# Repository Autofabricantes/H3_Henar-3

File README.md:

Hi! Welcome to the **_Henar#3 Wiki_**, please read carefully this welcome page that describes the full content of the _Wiki_.

This repository is still under construction (after many months, I know :'( ) Please if whatever doubt you have is not yet solved contact us somehow (email, Github, etc)

# Project Scope
The **_Henar#3_** is a _Open Source_ MIDI percussion instrument designed to perform live. Its main characteristics are:
* **Open Source:** The **_Henar#3_** has been designed and build with **_Open Source_** HW and SW and using accesible manufacturing technologies in order for it to be very affordable and easily moded.
* **Build Flexibility:** The **_Henar#3_** has been designed to allow a large number of different configurations (HMI elements in order to cope with the specific necessities of each user.
* **Stand Alone:** The **_Henar#3_** is an instrument designed to be played live, therefore it is a _Plug&Play_ device which does not need of extra elements to be played.
* **Periperic Flexibility:** Besides being a _Plug&Play_ device, the **_Henar#3_** allows its connection with other sound devices such as speakers and alternative MIDI devices.

# History and Collaborators
The **_Henar#3_** is part of a longer project started by the **_Celeo Proyectos_** and **_Un Instrumento para Henar_** in 2015. Its initial objective is to build a proper adapted instrument for Henar, a woman from Cuenca (Spain) that plays in an orchestra.

Apart from the instrument (which has two previous versions which will be described later) the project aims to build up a platform for the community of developers, users and enthusiasts to work together towards new ways to socialize with music and make it accesible for everyone. This is achieved not only through the development of the instrument itself but also through the creation of didactic materials and the organization of events such as **_DiverS+S 2017_** (http://www.diversos.eu/), where various projects were presented and put in common, in order to create links and an active net.

The collaborators of this project are:
## Celeo Proyectos

## Un instrumento para Henar

### Website: www.centroceleo.es/henar
### Contact: uninstrumentoparahenar@gmail.com

## Autofabricantes
**_Autofabricantes_** in an association based in _Medialab-Prado_, Madrid. It develops several _Open Source_ technological solutions in the medical and accesibility field. It's main development lines right now are:
* Myoelectric Hand Prothesis for children.
* 3D printed hand prosthesis for children (both experimental like __SuperGizz__ and standard).
* **_Henar#3_** instrument (The one this Wiki covers).

### Website: www.autofabricantes.org
### Contact: info@autofabricantes.org

## Escuela de Oficios Electrosonoros
_**Escuela de Oficios Electrosonoros**_ (in eng. _**School for Electrosonic Crafts**_) is an artistic and educational project that works to make electronic music (or music made with technology in general) accesible to everyone. 

*  Elaborate a feministic (or better just... diverse) history of electronic music.
*  Develop pedagogical tools for teaching electronic music in schools.
*  Research about accessibility of electronic music.

### Website: www.oficioselectrosonoros.org
### Contact: gurrupibaby@gmail.com

# About the previous Henar (Henar#1, Henar#2)
The Un instrumento para Henar project has already developed two previous versions of the instruments.

## Henar#1: [HERE LINK]
## Henar#2: [HERE LINK]

The **_Henar#3_** improvement objetives are:
* Increase System flexibility.
* Easier Assembly and manufacturing.
* Easier MIDI configuration.
* Improved ergonomy.

# Scope of the Wiki
This _Wiki_ aims to concentrate all the knowledge of the project. This covers:
* Global description of the project and its subsystems.
* Description of all the files in the repository.
* Description of all the elements and their evolution.
* **Assembly Guide** of all the elements (HW, SW, Mechanical).
* Tutorials and other didactic material.

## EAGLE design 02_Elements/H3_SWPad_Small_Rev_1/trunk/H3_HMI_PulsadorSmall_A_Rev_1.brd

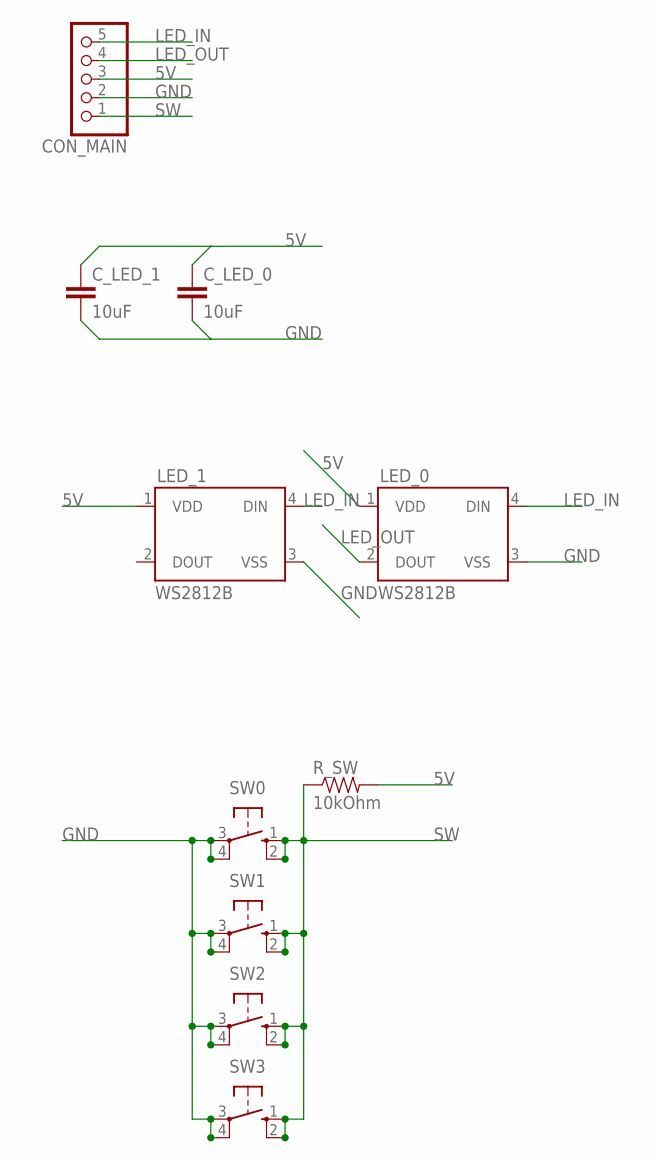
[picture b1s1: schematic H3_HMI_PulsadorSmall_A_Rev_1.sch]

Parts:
CON_MAIN: PINHD-1X5/90; 1X05/90
C_LED_0, C_LED_1: 10uF; C1206
LED_0, LED_1: WS2812B
R_SW: 10kOhm; 1206
SW0, SW1, SW2, SW3: 10-XX; B3F-10XX

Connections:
5V: CON_MAIN.3, C_LED_0.1, C_LED_1.1, LED_0.1 (VDD), LED_1.1 (VDD), R_SW.2
GND: CON_MAIN.2, C_LED_0.2, C_LED_1.2, LED_0.3 (VSS), LED_1.3 (VSS), SW0.3, SW0.4 (P1), SW1.3, SW1.4 (P1), SW2.3, SW2.4 (P1), SW3.3, SW3.4 (P1)
LED_IN: CON_MAIN.5, LED_0.4 (DIN), LED_1.4 (DIN)
LED_OUT: CON_MAIN.4, LED_0.2 (DOUT)
SW: CON_MAIN.1, R_SW.1, SW0.1 (S), SW0.2 (S1), SW1.1 (S), SW1.2 (S1), SW2.1 (S), SW2.2 (S1), SW3.1 (S), SW3.2 (S1)

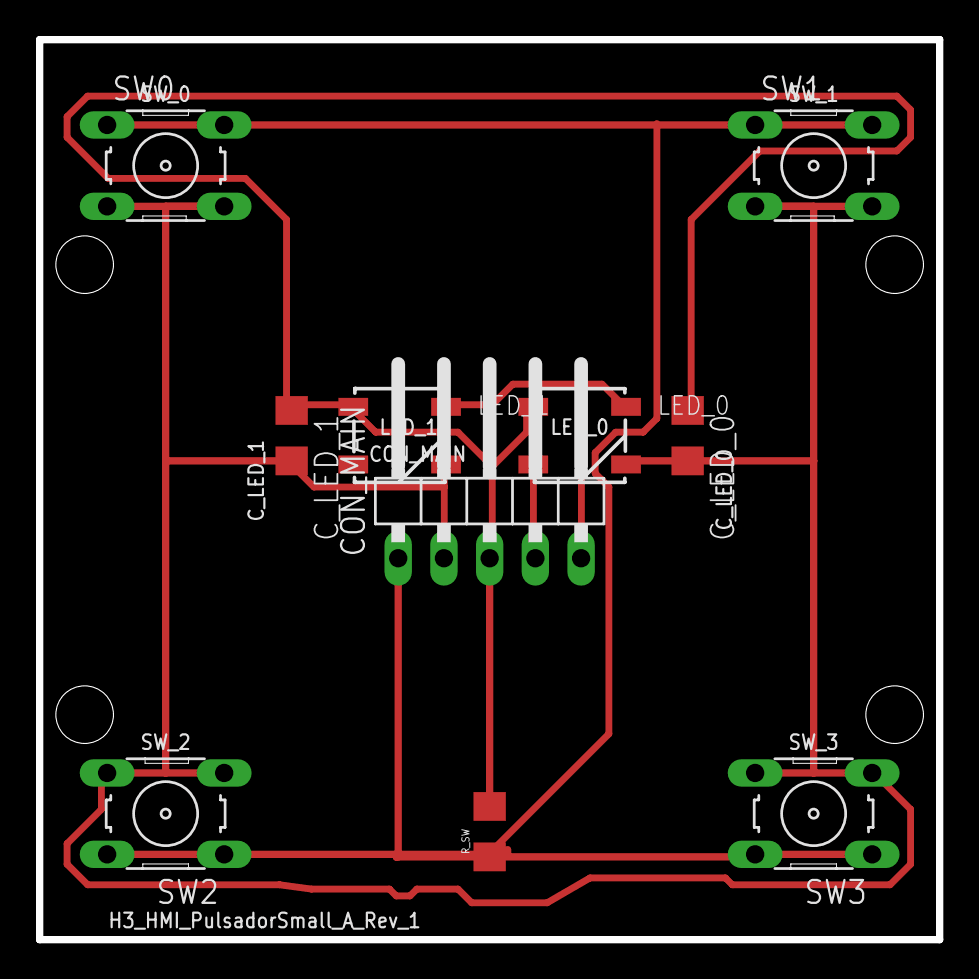
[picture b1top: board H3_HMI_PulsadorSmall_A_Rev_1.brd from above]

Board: 2 copper layers, 50.0 x 50.0 mm, 10 parts (0 on the bottom side), 5 nets.

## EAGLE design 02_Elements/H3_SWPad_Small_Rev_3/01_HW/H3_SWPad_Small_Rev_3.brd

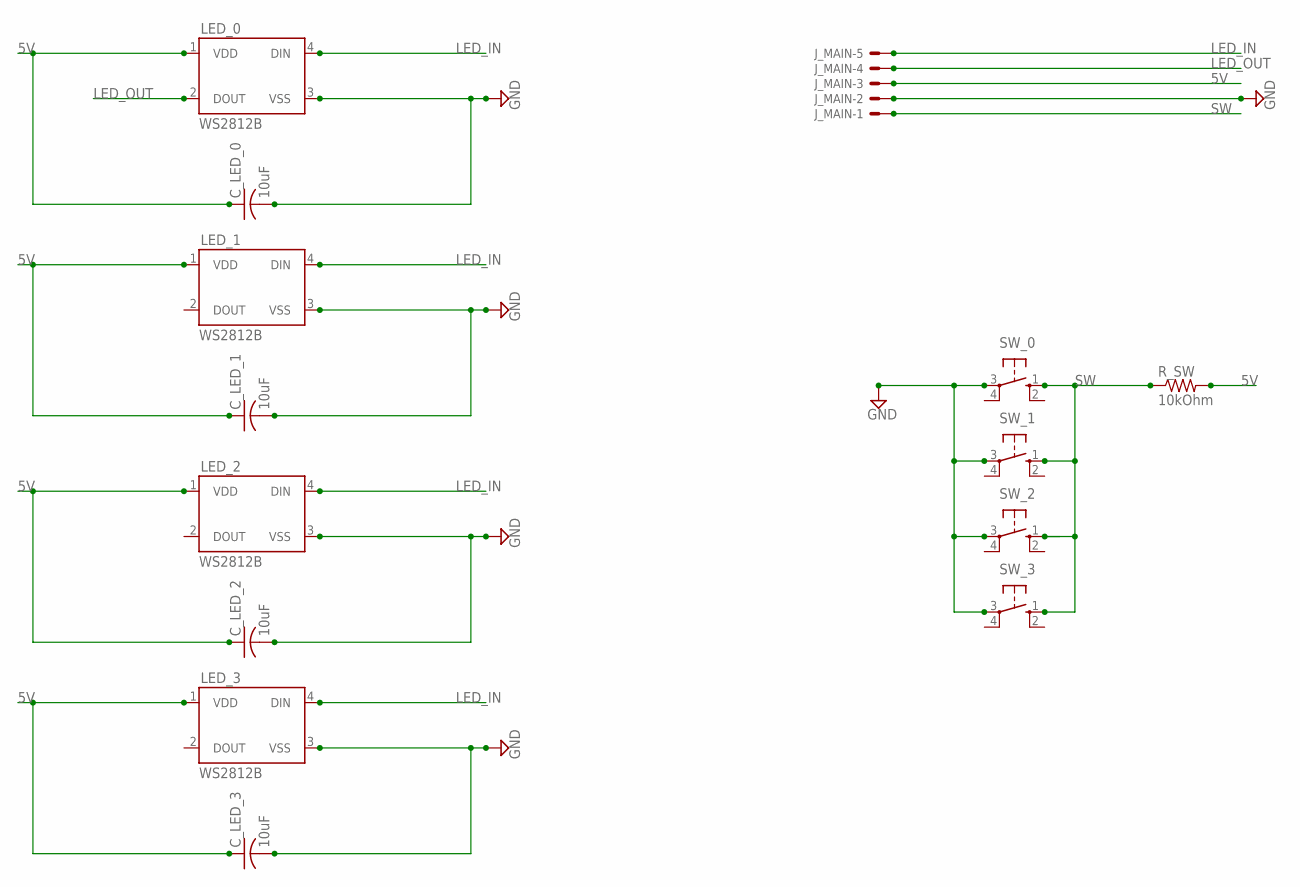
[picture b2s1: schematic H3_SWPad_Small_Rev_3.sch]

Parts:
C_LED_0, C_LED_1, C_LED_2, C_LED_3: 10uF; C1206K
J_MAIN: 22-05-7058-05; 7395-05
LED_0, LED_1, LED_2, LED_3: WS2812B
R_SW: 10kOhm; R1206W
SW_0, SW_1, SW_2, SW_3: 10-XX; B3F-10XX

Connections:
5V: C_LED_0.1, C_LED_1.1, C_LED_2.1, C_LED_3.1, J_MAIN.3, LED_0.1 (VDD), LED_1.1 (VDD), LED_2.1 (VDD), LED_3.1 (VDD), R_SW.2
GND: C_LED_0.2, C_LED_1.2, C_LED_2.2, C_LED_3.2, J_MAIN.2, LED_0.3 (VSS), LED_1.3 (VSS), LED_2.3 (VSS), LED_3.3 (VSS), SW_0.3, SW_1.3, SW_2.3, SW_3.3
LED_IN: J_MAIN.5, LED_0.4 (DIN), LED_1.4 (DIN), LED_2.4 (DIN), LED_3.4 (DIN)
LED_OUT: J_MAIN.4, LED_0.2 (DOUT)
SW: J_MAIN.1, R_SW.1, SW_0.1 (S), SW_1.1 (S), SW_2.1 (S), SW_3.1 (S)

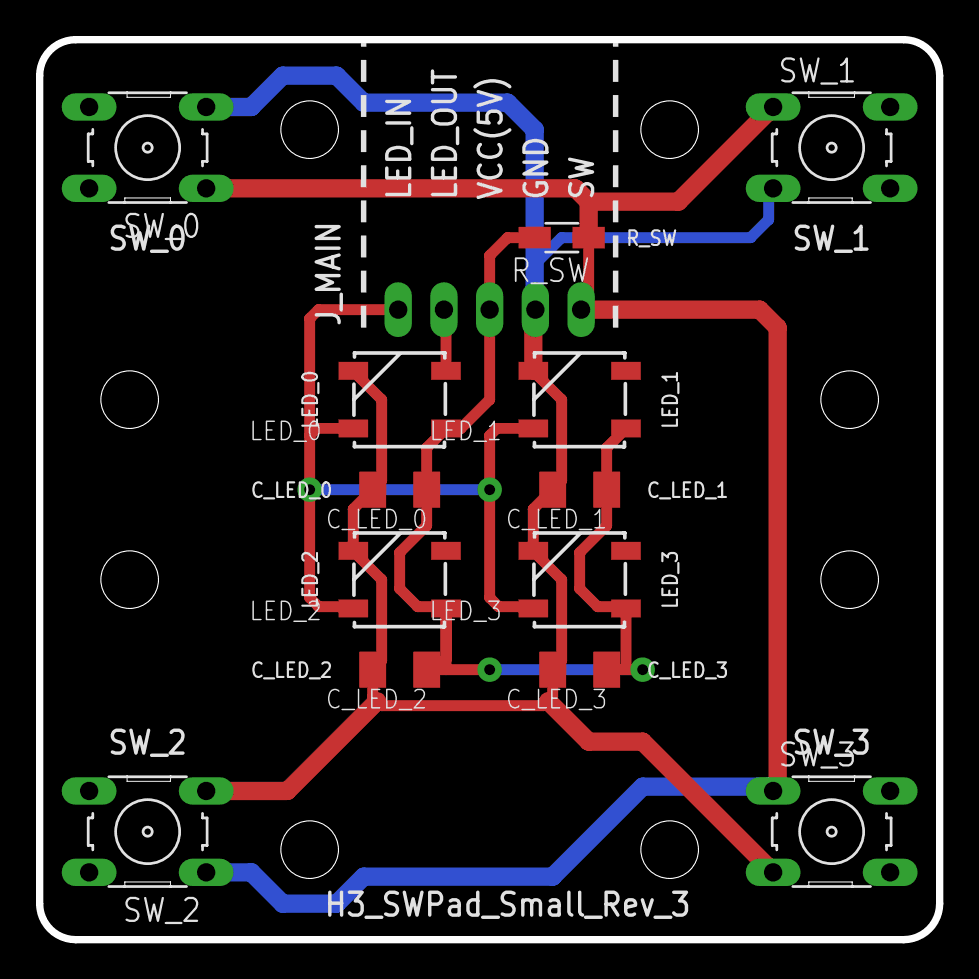
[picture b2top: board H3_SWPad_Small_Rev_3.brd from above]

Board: 2 copper layers, 50.0 x 50.0 mm, 14 parts (1 on the bottom side), 5 nets.

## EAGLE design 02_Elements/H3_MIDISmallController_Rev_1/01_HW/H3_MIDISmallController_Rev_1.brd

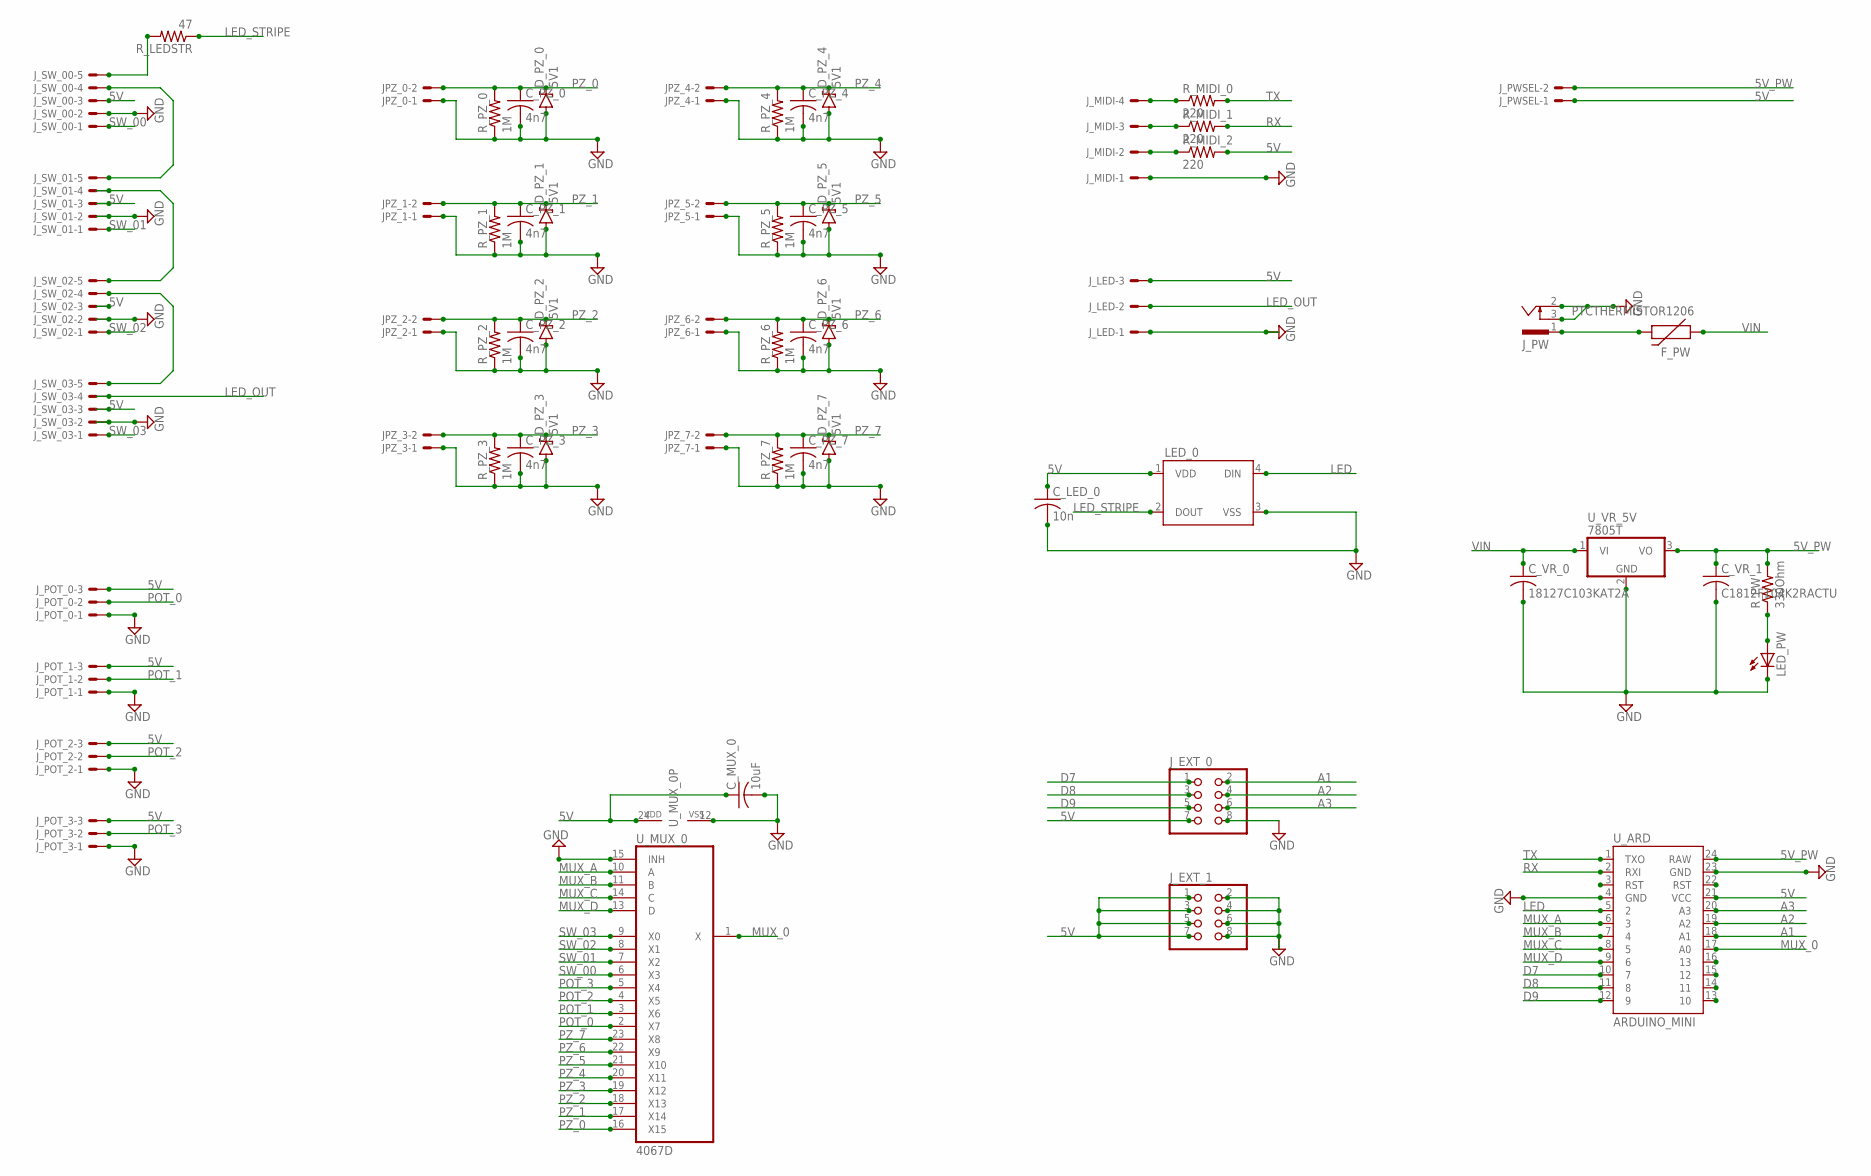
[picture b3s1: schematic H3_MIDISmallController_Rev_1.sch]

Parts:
C_LED_0: 10n; C1206
C_MUX_0: 10uF; C1206K
C_PZ_0, C_PZ_1, C_PZ_2, C_PZ_3, C_PZ_4, C_PZ_5, C_PZ_6, C_PZ_7: 4n7; C1206
C_VR_0: 18127C103KAT2A; C1206
C_VR_1: C1812F104K2RACTU; C1206
D_PZ_0, D_PZ_1, D_PZ_2, D_PZ_3, D_PZ_4, D_PZ_5, D_PZ_6, D_PZ_7: 5V1; DIODE-BZT52
F_PW: PTCTHERMISTOR1206; PTC-1206
JPZ_0, JPZ_1, JPZ_2, JPZ_3, JPZ_4, JPZ_5, JPZ_6, JPZ_7: 22-05-7028-02; 7395-02
J_EXT_0, J_EXT_1: PINHD-2X4/90; 2X04/90
J_LED: 22-05-7038-03; 7395-03
J_MIDI: 22-05-7048-04; 7395-04
J_POT_0, J_POT_1, J_POT_2, J_POT_3: 22-05-7038-03; 7395-03
J_PW: SCD-014A; SCD-014-A
J_PWSEL: 22-05-7028-02; 7395-02
J_SW_00, J_SW_01, J_SW_02, J_SW_03: 22-05-7058-05; 7395-05
LED_0: WS2812B
LED_PW: LEDSMT1206; 1206
R_LEDSTR: 47; M1206
R_MIDI_0, R_MIDI_1, R_MIDI_2: 220; M1206
R_PW: 330Ohm; M1206
R_PZ_0, R_PZ_1, R_PZ_2, R_PZ_3, R_PZ_4, R_PZ_5, R_PZ_6, R_PZ_7: 1M; M1206
U_ARD: ARDUINO_MINI
U_MUX_0: 4067D; SO24W
U_VR_5V: 7805T; TO220H

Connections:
5V: C_LED_0.1, C_MUX_0.1, J_EXT_0.7, J_EXT_1.1, J_EXT_1.3, J_EXT_1.5, J_EXT_1.7, J_LED.3, J_POT_0.3, J_POT_1.3, J_POT_2.3, J_POT_3.3, J_PWSEL.1, J_SW_00.3, J_SW_01.3, J_SW_02.3, J_SW_03.3, LED_0.1 (VDD), R_MIDI_2.2, U_ARD.21 (VCC), U_MUX_0.24 (VDD)
5V_PW: C_VR_1.1, J_PWSEL.2, R_PW.2, U_ARD.24 (RAW), U_VR_5V.3 (VO)
A1: J_EXT_0.2, U_ARD.18 (A1)
A2: J_EXT_0.4, U_ARD.19 (A2)
A3: J_EXT_0.6, U_ARD.20 (A3)
D7: J_EXT_0.1, U_ARD.10 (7)
D8: J_EXT_0.3, U_ARD.11 (8)
D9: J_EXT_0.5, U_ARD.12 (9)
GND: C_LED_0.2, C_MUX_0.2, C_PZ_0.2, C_PZ_1.2, C_PZ_2.2, C_PZ_3.2, C_PZ_4.2, C_PZ_5.2, C_PZ_6.2, C_PZ_7.2, C_VR_0.2, C_VR_1.2, D_PZ_0.A, D_PZ_1.A, D_PZ_2.A, D_PZ_3.A, D_PZ_4.A, D_PZ_5.A, D_PZ_6.A, D_PZ_7.A, JPZ_0.1, JPZ_1.1, JPZ_2.1, JPZ_3.1, JPZ_4.1, JPZ_5.1, JPZ_6.1, JPZ_7.1, J_EXT_0.8, J_EXT_1.2, J_EXT_1.4, J_EXT_1.6, J_EXT_1.8, J_LED.1, J_MIDI.1, J_POT_0.1, J_POT_1.1, J_POT_2.1, J_POT_3.1, J_PW.2, J_PW.3, J_SW_00.2, J_SW_01.2, J_SW_02.2, J_SW_03.2, LED_0.3 (VSS), LED_PW.C, R_PZ_0.1, R_PZ_1.1, R_PZ_2.1, R_PZ_3.1, R_PZ_4.1, R_PZ_5.1, R_PZ_6.1, R_PZ_7.1, U_ARD.4 (GND), U_ARD.23 (GND), U_MUX_0.12 (VSS), U_MUX_0.15 (INH), U_VR_5V.2 (GND)
LED: LED_0.4 (DIN), U_ARD.5 (2)
LED_IN2: J_SW_01.4, J_SW_02.5
LED_OUT: J_LED.2, J_SW_03.4
LED_STRIPE: LED_0.2 (DOUT), R_LEDSTR.1
MUX_0: U_ARD.17 (A0), U_MUX_0.1 (X)
MUX_A: U_ARD.6 (3), U_MUX_0.10 (A)
MUX_B: U_ARD.7 (4), U_MUX_0.11 (B)
MUX_C: U_ARD.8 (5), U_MUX_0.14 (C)
MUX_D: U_ARD.9 (6), U_MUX_0.13 (D)
unnamed: LED_PW.A, R_PW.1
unnamed: J_SW_00.4, J_SW_01.5
unnamed: J_SW_00.5, R_LEDSTR.2
unnamed: J_SW_02.4, J_SW_03.5
unnamed: F_PW.2, J_PW.1
unnamed: J_MIDI.2, R_MIDI_2.1
unnamed: J_MIDI.3, R_MIDI_1.1
unnamed: J_MIDI.4, R_MIDI_0.1
POT_0: J_POT_0.2, U_MUX_0.2 (X7)
POT_1: J_POT_1.2, U_MUX_0.3 (X6)
POT_2: J_POT_2.2, U_MUX_0.4 (X5)
POT_3: J_POT_3.2, U_MUX_0.5 (X4)
PZ_0: C_PZ_0.1, D_PZ_0.C, JPZ_0.2, R_PZ_0.2, U_MUX_0.16 (X15)
PZ_1: C_PZ_1.1, D_PZ_1.C, JPZ_1.2, R_PZ_1.2, U_MUX_0.17 (X14)
PZ_2: C_PZ_2.1, D_PZ_2.C, JPZ_2.2, R_PZ_2.2, U_MUX_0.18 (X13)
PZ_3: C_PZ_3.1, D_PZ_3.C, JPZ_3.2, R_PZ_3.2, U_MUX_0.19 (X12)
PZ_4: C_PZ_4.1, D_PZ_4.C, JPZ_4.2, R_PZ_4.2, U_MUX_0.20 (X11)
PZ_5: C_PZ_5.1, D_PZ_5.C, JPZ_5.2, R_PZ_5.2, U_MUX_0.21 (X10)
PZ_6: C_PZ_6.1, D_PZ_6.C, JPZ_6.2, R_PZ_6.2, U_MUX_0.22 (X9)
PZ_7: C_PZ_7.1, D_PZ_7.C, JPZ_7.2, R_PZ_7.2, U_MUX_0.23 (X8)
RX: R_MIDI_1.2, U_ARD.2 (RXI)
SW_00: J_SW_00.1, U_MUX_0.6 (X3)
SW_01: J_SW_01.1, U_MUX_0.7 (X2)
SW_02: J_SW_02.1, U_MUX_0.8 (X1)
SW_03: J_SW_03.1, U_MUX_0.9 (X0)
TX: R_MIDI_0.2, U_ARD.1 (TXO)
VIN: C_VR_0.1, F_PW.1, U_VR_5V.1 (VI)

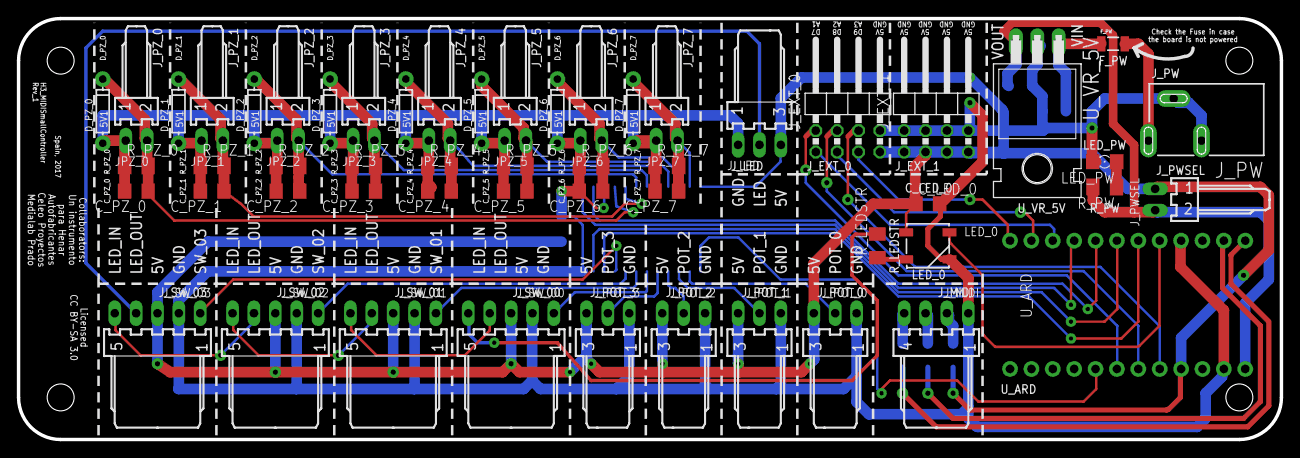
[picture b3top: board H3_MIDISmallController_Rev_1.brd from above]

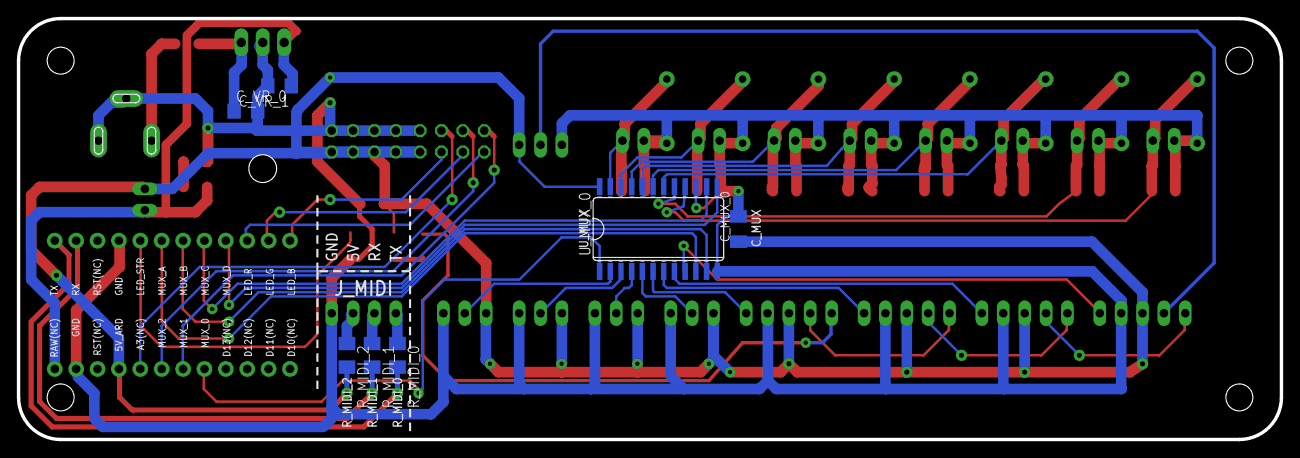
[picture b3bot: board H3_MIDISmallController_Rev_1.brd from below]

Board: 2 copper layers, 150.0 x 50.0 mm, 61 parts (7 on the bottom side), 45 nets.

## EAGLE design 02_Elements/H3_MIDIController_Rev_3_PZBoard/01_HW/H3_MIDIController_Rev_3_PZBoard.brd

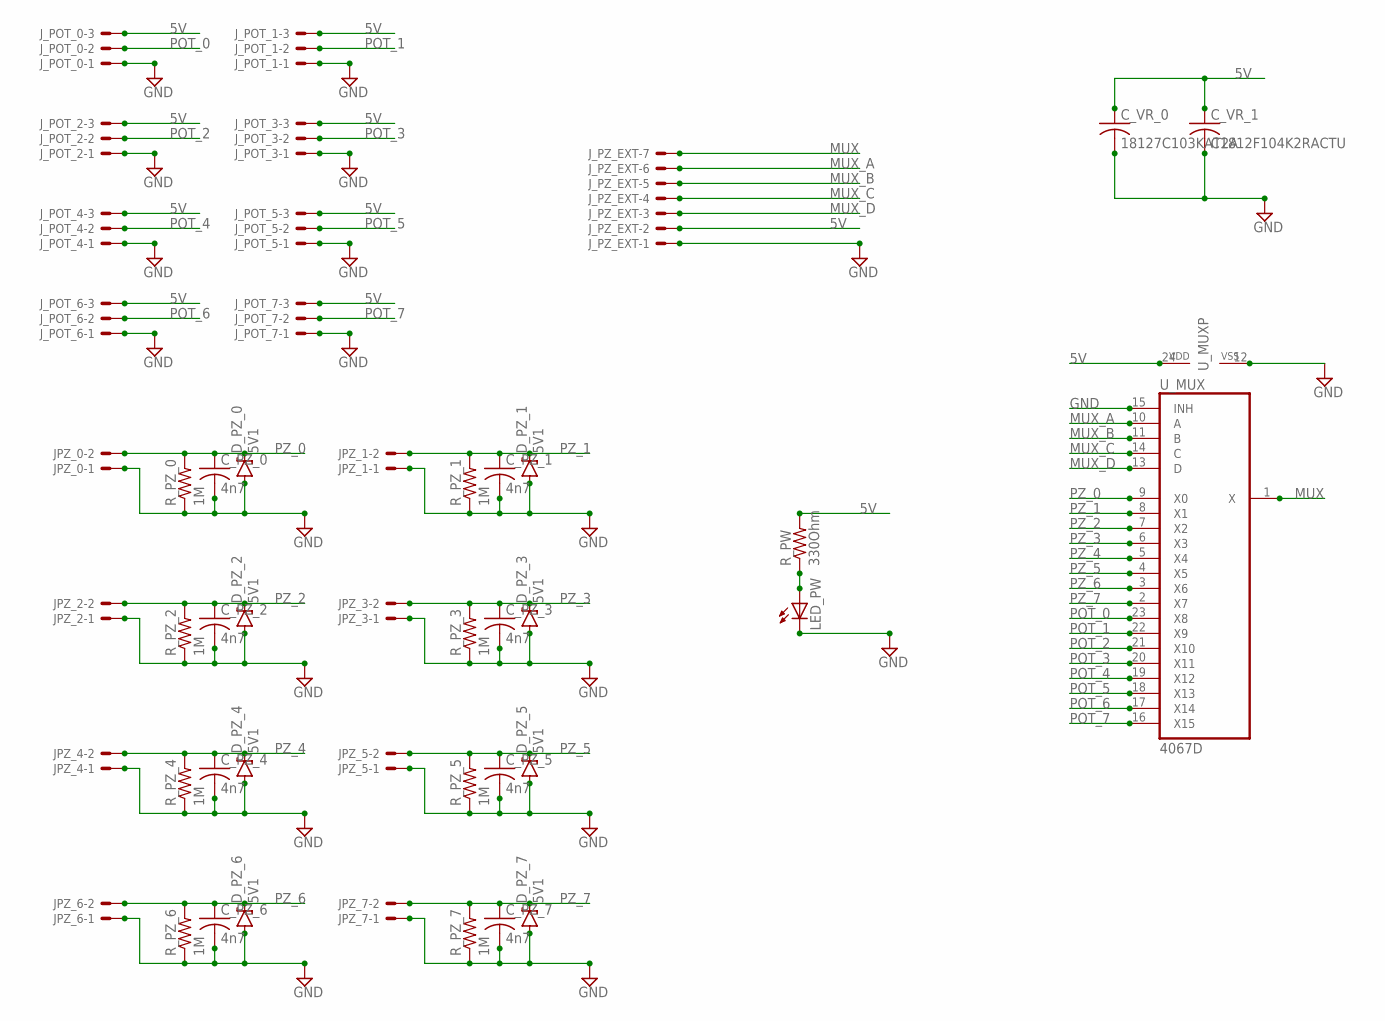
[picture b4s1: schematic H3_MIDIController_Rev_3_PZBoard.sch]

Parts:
C_PZ_0, C_PZ_1, C_PZ_2, C_PZ_3, C_PZ_4, C_PZ_5, C_PZ_6, C_PZ_7: 4n7; C1206
C_VR_0: 18127C103KAT2A; C1812K
C_VR_1: C1812F104K2RACTU; C1812K
D_PZ_0, D_PZ_1, D_PZ_2, D_PZ_3, D_PZ_4, D_PZ_5, D_PZ_6, D_PZ_7: 5V1; DIODE-BZT52
JPZ_0, JPZ_1, JPZ_2, JPZ_3, JPZ_4, JPZ_5, JPZ_6, JPZ_7: 22-05-7028-02; 7395-02
J_POT_0, J_POT_1, J_POT_2, J_POT_3, J_POT_4, J_POT_5, J_POT_6, J_POT_7: 22-05-7038-03; 7395-03
J_PZ_EXT: 22-05-7078-07; 7395-07
LED_PW: LEDSMT1206; 1206
R_PW: 330Ohm; M1206
R_PZ_0, R_PZ_1, R_PZ_2, R_PZ_3, R_PZ_4, R_PZ_5, R_PZ_6, R_PZ_7: 1M; M1206
U_MUX: 4067D; SO24W

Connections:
5V: C_VR_0.1, C_VR_1.1, J_POT_0.3, J_POT_1.3, J_POT_2.3, J_POT_3.3, J_POT_4.3, J_POT_5.3, J_POT_6.3, J_POT_7.3, J_PZ_EXT.2, R_PW.2, U_MUX.24 (VDD)
GND: C_PZ_0.2, C_PZ_1.2, C_PZ_2.2, C_PZ_3.2, C_PZ_4.2, C_PZ_5.2, C_PZ_6.2, C_PZ_7.2, C_VR_0.2, C_VR_1.2, D_PZ_0.A, D_PZ_1.A, D_PZ_2.A, D_PZ_3.A, D_PZ_4.A, D_PZ_5.A, D_PZ_6.A, D_PZ_7.A, JPZ_0.1, JPZ_1.1, JPZ_2.1, JPZ_3.1, JPZ_4.1, JPZ_5.1, JPZ_6.1, JPZ_7.1, J_POT_0.1, J_POT_1.1, J_POT_2.1, J_POT_3.1, J_POT_4.1, J_POT_5.1, J_POT_6.1, J_POT_7.1, J_PZ_EXT.1, LED_PW.C, R_PZ_0.1, R_PZ_1.1, R_PZ_2.1, R_PZ_3.1, R_PZ_4.1, R_PZ_5.1, R_PZ_6.1, R_PZ_7.1, U_MUX.12 (VSS), U_MUX.15 (INH)
MUX: J_PZ_EXT.7, U_MUX.1 (X)
MUX_A: J_PZ_EXT.6, U_MUX.10 (A)
MUX_B: J_PZ_EXT.5, U_MUX.11 (B)
MUX_C: J_PZ_EXT.4, U_MUX.14 (C)
MUX_D: J_PZ_EXT.3, U_MUX.13 (D)
unnamed: LED_PW.A, R_PW.1
POT_0: J_POT_0.2, U_MUX.23 (X8)
POT_1: J_POT_1.2, U_MUX.22 (X9)
POT_2: J_POT_2.2, U_MUX.21 (X10)
POT_3: J_POT_3.2, U_MUX.20 (X11)
POT_4: J_POT_4.2, U_MUX.19 (X12)
POT_5: J_POT_5.2, U_MUX.18 (X13)
POT_6: J_POT_6.2, U_MUX.17 (X14)
POT_7: J_POT_7.2, U_MUX.16 (X15)
PZ_0: C_PZ_0.1, D_PZ_0.C, JPZ_0.2, R_PZ_0.2, U_MUX.9 (X0)
PZ_1: C_PZ_1.1, D_PZ_1.C, JPZ_1.2, R_PZ_1.2, U_MUX.8 (X1)
PZ_2: C_PZ_2.1, D_PZ_2.C, JPZ_2.2, R_PZ_2.2, U_MUX.7 (X2)
PZ_3: C_PZ_3.1, D_PZ_3.C, JPZ_3.2, R_PZ_3.2, U_MUX.6 (X3)
PZ_4: C_PZ_4.1, D_PZ_4.C, JPZ_4.2, R_PZ_4.2, U_MUX.5 (X4)
PZ_5: C_PZ_5.1, D_PZ_5.C, JPZ_5.2, R_PZ_5.2, U_MUX.4 (X5)
PZ_6: C_PZ_6.1, D_PZ_6.C, JPZ_6.2, R_PZ_6.2, U_MUX.3 (X6)
PZ_7: C_PZ_7.1, D_PZ_7.C, JPZ_7.2, R_PZ_7.2, U_MUX.2 (X7)

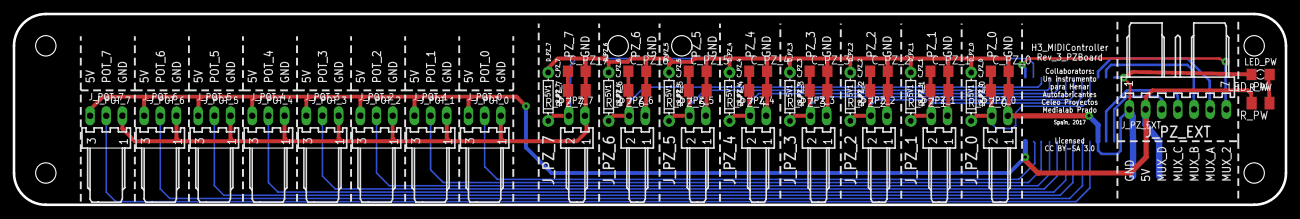
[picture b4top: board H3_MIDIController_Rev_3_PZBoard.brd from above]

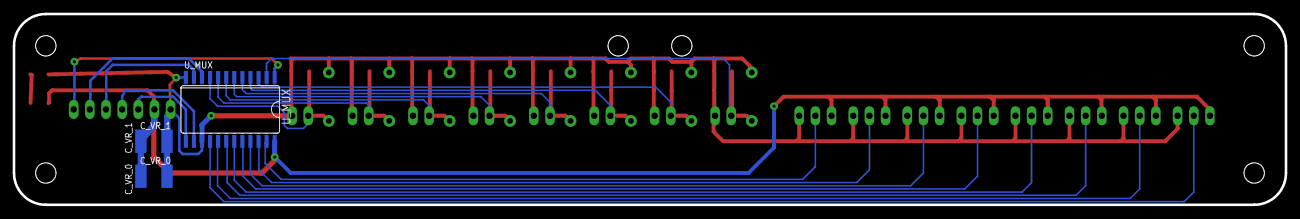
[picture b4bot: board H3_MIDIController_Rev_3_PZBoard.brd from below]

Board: 2 copper layers, 200.0 x 30.0 mm, 46 parts (3 on the bottom side), 24 nets.

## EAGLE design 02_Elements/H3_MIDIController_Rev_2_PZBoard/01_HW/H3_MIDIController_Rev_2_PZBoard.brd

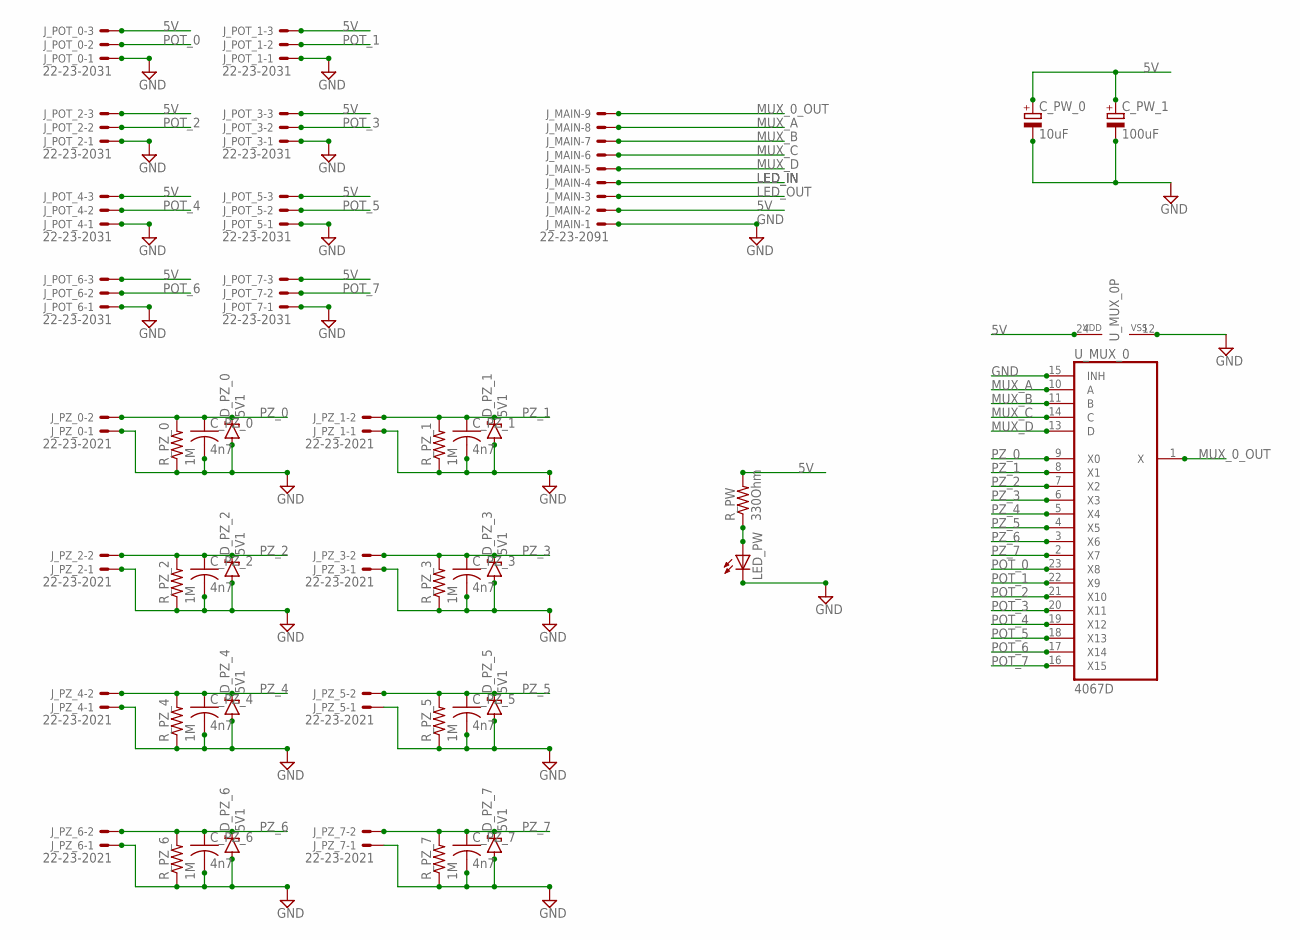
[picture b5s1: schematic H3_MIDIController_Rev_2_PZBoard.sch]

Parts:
C_PW_0: 10uF; TT2D6L
C_PW_1: 100uF; TT2D6L
C_PZ_0, C_PZ_1, C_PZ_2, C_PZ_3, C_PZ_4, C_PZ_5, C_PZ_6, C_PZ_7: 4n7; C1206
D_PZ_0, D_PZ_1, D_PZ_2, D_PZ_3, D_PZ_4, D_PZ_5, D_PZ_6, D_PZ_7: 5V1; DIODE-BZT52
J_MAIN: 22-23-2091
J_POT_0, J_POT_1, J_POT_2, J_POT_3, J_POT_4, J_POT_5, J_POT_6, J_POT_7: 22-23-2031
J_PZ_0, J_PZ_1, J_PZ_2, J_PZ_3, J_PZ_4, J_PZ_5, J_PZ_6, J_PZ_7: 22-23-2021
LED_PW: LEDSMT1206; 1206
R_PW: 330Ohm; M1206
R_PZ_0, R_PZ_1, R_PZ_2, R_PZ_3, R_PZ_4, R_PZ_5, R_PZ_6, R_PZ_7: 1M; M1206
U_MUX_0: 4067D; SO24W

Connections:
5V: C_PW_0.+, C_PW_1.+, J_MAIN.2, J_POT_0.3, J_POT_1.3, J_POT_2.3, J_POT_3.3, J_POT_4.3, J_POT_5.3, J_POT_6.3, J_POT_7.3, R_PW.2, U_MUX_0.24 (VDD)
GND: C_PW_0.-, C_PW_1.-, C_PZ_0.2, C_PZ_1.2, C_PZ_2.2, C_PZ_3.2, C_PZ_4.2, C_PZ_5.2, C_PZ_6.2, C_PZ_7.2, D_PZ_0.A, D_PZ_1.A, D_PZ_2.A, D_PZ_3.A, D_PZ_4.A, D_PZ_5.A, D_PZ_6.A, D_PZ_7.A, J_MAIN.1, J_POT_0.1, J_POT_1.1, J_POT_2.1, J_POT_3.1, J_POT_4.1, J_POT_5.1, J_POT_6.1, J_POT_7.1, J_PZ_0.1, J_PZ_1.1, J_PZ_2.1, J_PZ_3.1, J_PZ_4.1, J_PZ_5.1, J_PZ_6.1, J_PZ_7.1, LED_PW.C, R_PZ_0.1, R_PZ_1.1, R_PZ_2.1, R_PZ_3.1, R_PZ_4.1, R_PZ_5.1, R_PZ_6.1, R_PZ_7.1, U_MUX_0.12 (VSS), U_MUX_0.15 (INH)
LED_IN: J_MAIN.4
LED_OUT: J_MAIN.3
MUX_0_OUT: J_MAIN.9, U_MUX_0.1 (X)
MUX_A: J_MAIN.8, U_MUX_0.10 (A)
MUX_B: J_MAIN.7, U_MUX_0.11 (B)
MUX_C: J_MAIN.6, U_MUX_0.14 (C)
MUX_D: J_MAIN.5, U_MUX_0.13 (D)
unnamed: LED_PW.A, R_PW.1
POT_0: J_POT_0.2, U_MUX_0.23 (X8)
POT_1: J_POT_1.2, U_MUX_0.22 (X9)
POT_2: J_POT_2.2, U_MUX_0.21 (X10)
POT_3: J_POT_3.2, U_MUX_0.20 (X11)
POT_4: J_POT_4.2, U_MUX_0.19 (X12)
POT_5: J_POT_5.2, U_MUX_0.18 (X13)
POT_6: J_POT_6.2, U_MUX_0.17 (X14)
POT_7: J_POT_7.2, U_MUX_0.16 (X15)
PZ_0: C_PZ_0.1, D_PZ_0.C, J_PZ_0.2, R_PZ_0.2, U_MUX_0.9 (X0)
PZ_1: C_PZ_1.1, D_PZ_1.C, J_PZ_1.2, R_PZ_1.2, U_MUX_0.8 (X1)
PZ_2: C_PZ_2.1, D_PZ_2.C, J_PZ_2.2, R_PZ_2.2, U_MUX_0.7 (X2)
PZ_3: C_PZ_3.1, D_PZ_3.C, J_PZ_3.2, R_PZ_3.2, U_MUX_0.6 (X3)
PZ_4: C_PZ_4.1, D_PZ_4.C, J_PZ_4.2, R_PZ_4.2, U_MUX_0.5 (X4)
PZ_5: C_PZ_5.1, D_PZ_5.C, J_PZ_5.2, R_PZ_5.2, U_MUX_0.4 (X5)
PZ_6: C_PZ_6.1, D_PZ_6.C, J_PZ_6.2, R_PZ_6.2, U_MUX_0.3 (X6)
PZ_7: C_PZ_7.1, D_PZ_7.C, J_PZ_7.2, R_PZ_7.2, U_MUX_0.2 (X7)

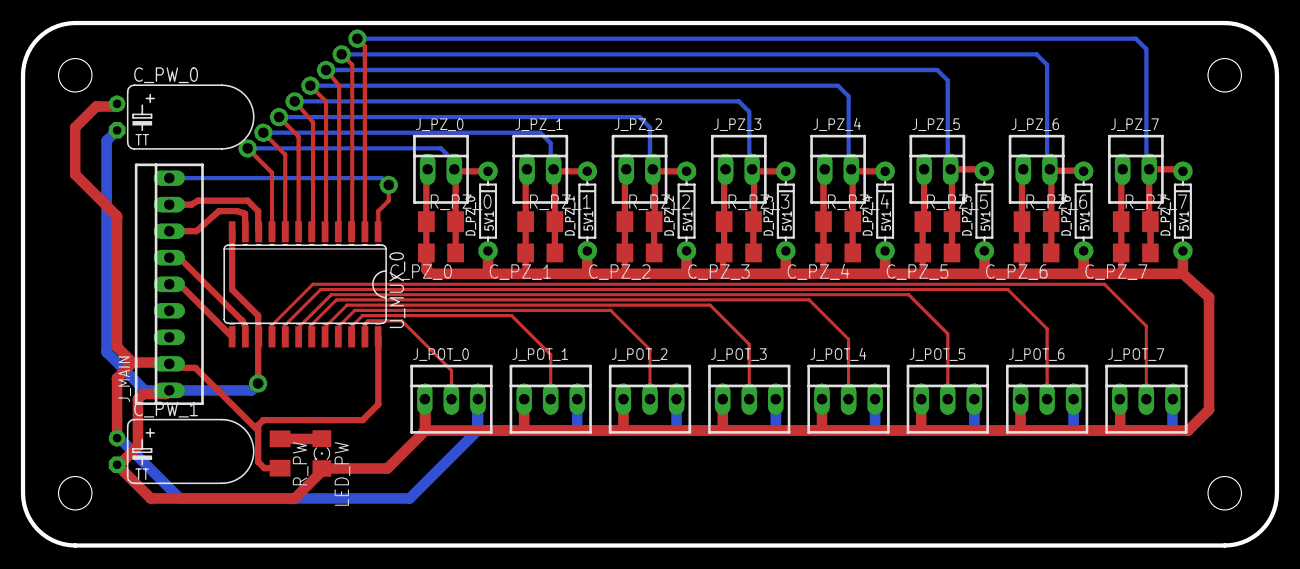
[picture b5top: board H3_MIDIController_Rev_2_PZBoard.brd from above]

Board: 2 copper layers, 120.0 x 50.0 mm, 46 parts (0 on the bottom side), 24 nets.

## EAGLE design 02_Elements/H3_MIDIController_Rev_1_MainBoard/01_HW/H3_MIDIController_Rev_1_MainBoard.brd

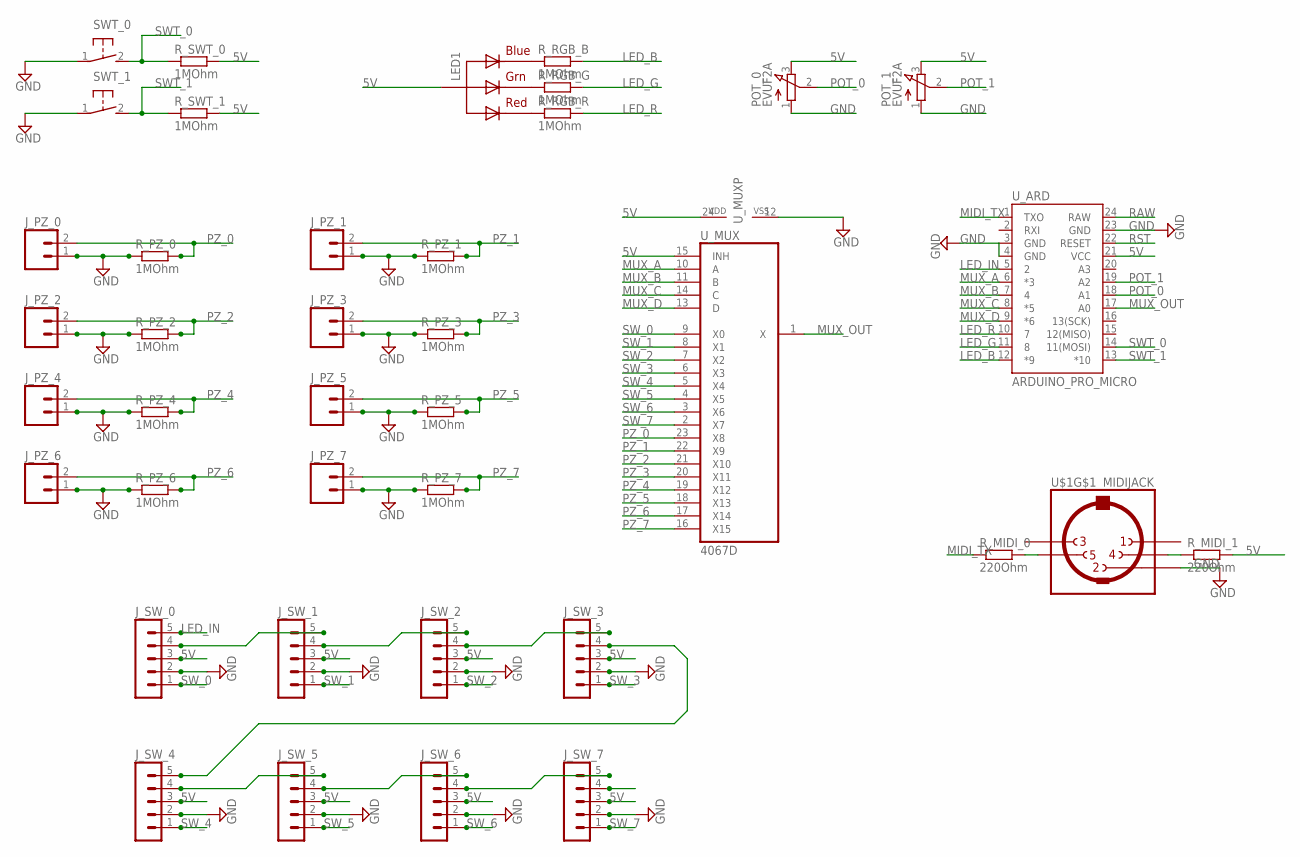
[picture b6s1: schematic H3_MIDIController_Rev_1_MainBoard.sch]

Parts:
J_PZ_0, J_PZ_1, J_PZ_2, J_PZ_3, J_PZ_4, J_PZ_5, J_PZ_6, J_PZ_7: MA02; 02PA
J_SW_0, J_SW_1, J_SW_2, J_SW_3, J_SW_4, J_SW_5, J_SW_6, J_SW_7: MA05-1
LED1: RGBLED_CA-5MM; LED5MMRGB
POT_0, POT_1: EVUF2A; EVUF
R_MIDI_0, R_MIDI_1: 220Ohm; M1206
R_PZ_0, R_PZ_1, R_PZ_2, R_PZ_3, R_PZ_4, R_PZ_5, R_PZ_6, R_PZ_7: 1MOhm; M1206
R_RGB_B: 1MOhm; M1206
R_RGB_G: 1MOhm; M1206
R_RGB_R: 1MOhm; M1206
R_SWT_0, R_SWT_1: 1MOhm; M1206
SWT_0, SWT_1: 31-XX; B3F-31XX
U$1: MIDIJACK; CP-2350
U_ARD: ARDUINO_PRO_MICRO
U_MUX: 4067D; SO24W

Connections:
5V: J_SW_0.3, J_SW_1.3, J_SW_2.3, J_SW_3.3, J_SW_4.3, J_SW_5.3, J_SW_6.3, J_SW_7.3, LED1.2 (VCC), POT_0.3 (E), POT_1.3 (E), R_MIDI_1.2, R_SWT_0.2, R_SWT_1.2, U_ARD.21 (VCC), U_MUX.15 (INH), U_MUX.24 (VDD)
GND: J_PZ_0.1, J_PZ_1.1, J_PZ_2.1, J_PZ_3.1, J_PZ_4.1, J_PZ_5.1, J_PZ_6.1, J_PZ_7.1, J_SW_0.2, J_SW_1.2, J_SW_2.2, J_SW_3.2, J_SW_4.2, J_SW_5.2, J_SW_6.2, J_SW_7.2, POT_0.1 (A), POT_1.1 (A), R_PZ_0.1, R_PZ_1.1, R_PZ_2.1, R_PZ_3.1, R_PZ_4.1, R_PZ_5.1, R_PZ_6.1, R_PZ_7.1, SWT_0.1, SWT_1.1, U$1.2, U_ARD.3 (GND), U_ARD.4 (GND), U_ARD.23 (GND), U_MUX.12 (VSS)
LED_B: R_RGB_B.2, U_ARD.12 (*9)
LED_G: R_RGB_G.2, U_ARD.11 (8)
LED_IN: J_SW_0.5, U_ARD.5 (2)
LED_R: R_RGB_R.2, U_ARD.10 (7)
MIDI_TX: R_MIDI_0.1, U_ARD.1 (TXO)
MUX_A: U_ARD.6 (*3), U_MUX.10 (A)
MUX_B: U_ARD.7 (4), U_MUX.11 (B)
MUX_C: U_ARD.8 (*5), U_MUX.14 (C)
MUX_D: U_ARD.9 (*6), U_MUX.13 (D)
MUX_OUT: U_ARD.17 (A0), U_MUX.1 (X)
unnamed: J_SW_1.4, J_SW_2.5
unnamed: J_SW_0.4, J_SW_1.5
unnamed: LED1.1 (RED), R_RGB_R.1
unnamed: J_SW_2.4, J_SW_3.5
unnamed: R_MIDI_0.2, U$1.5
unnamed: J_SW_3.4, J_SW_4.5
unnamed: LED1.3 (GREEN), R_RGB_G.1
unnamed: J_SW_4.4, J_SW_5.5
unnamed: J_SW_5.4, J_SW_6.5
unnamed: R_MIDI_1.1, U$1.4
unnamed: J_SW_6.4, J_SW_7.5
unnamed: LED1.4 (BLUE), R_RGB_B.1
POT_0: POT_0.2 (S), U_ARD.18 (A1)
POT_1: POT_1.2 (S), U_ARD.19 (A2)
PZ_0: J_PZ_0.2, R_PZ_0.2, U_MUX.23 (X8)
PZ_1: J_PZ_1.2, R_PZ_1.2, U_MUX.22 (X9)
PZ_2: J_PZ_2.2, R_PZ_2.2, U_MUX.21 (X10)
PZ_3: J_PZ_3.2, R_PZ_3.2, U_MUX.20 (X11)
PZ_4: J_PZ_4.2, R_PZ_4.2, U_MUX.19 (X12)
PZ_5: J_PZ_5.2, R_PZ_5.2, U_MUX.18 (X13)
PZ_6: J_PZ_6.2, R_PZ_6.2, U_MUX.17 (X14)
PZ_7: J_PZ_7.2, R_PZ_7.2, U_MUX.16 (X15)
RAW: U_ARD.24 (RAW)
RST: U_ARD.22 (RESET)
SWT_0: R_SWT_0.1, SWT_0.2 (S), U_ARD.14 (11(MOSI))
SWT_1: R_SWT_1.1, SWT_1.2 (S), U_ARD.13 (*10)
SW_0: J_SW_0.1, U_MUX.9 (X0)
SW_1: J_SW_1.1, U_MUX.8 (X1)
SW_2: J_SW_2.1, U_MUX.7 (X2)
SW_3: J_SW_3.1, U_MUX.6 (X3)
SW_4: J_SW_4.1, U_MUX.5 (X4)
SW_5: J_SW_5.1, U_MUX.4 (X5)
SW_6: J_SW_6.1, U_MUX.3 (X6)
SW_7: J_SW_7.1, U_MUX.2 (X7)

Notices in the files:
02_Elements/H3_MIDIController_Rev_3_MainBoard/01_HW/H3_MIDIController_Rev_3_MainBoard.brd:
CC BY-SA 3.0
parts and their libraries:
SparkFun-Boards: Licensing: Creative Commons ShareAlike 4.0 International - https://creativecommons.org/licenses/by-sa/4.0
